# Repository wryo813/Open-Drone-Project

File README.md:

# Open Drone Project
## 概要
このプロジェクトは、Arduinoプラットフォーム上で開発可能なドローン制御システムの構築を目的としています。
***
# ハードウェア
## 電源仕様
### USBバスパワー給電時
- USB Type-C(USB2.0)で供給を行う
- バッテリーの充電が行われる
- バッテリー給電からUSBバスパワー給電に自動的に切り替わる
- システム全体の消費電流が750mAを超えるとリセッタブルヒューズの抵抗値が上がる
- ESP32-WROOM-32とバッテリー残量IC以外のセンサが起動する
- モーターが回転しないようソフト側で制限をかける
### バッテリー給電時
- 供給能力1000mA 3Cの[リチウムイオン二次電池](http://www.kyohritsu.jp/eclib/OTHER/DATASHEET/BATT/dtp603450phr.pdf)から供給を行う
- モーター含むシステム全体に電力を供給する
- すべての負荷はバッテリー残量ICを通過して電力が供給される
- 全モーターの消費電流が3A(仮)を超えたらソフト側で制限をかける
### バッテリー充電
- バッテリー充電はMCP73831-2ATI/OTを用いて行う
- 最大充電電流はPROG-GND間抵抗5kΩで最大200mAに設定する
#### MCP73831-2ATI/OTの最大充電電流の設定([公式データシート](https://www.microchip.jp/docs/DS21984B_JP.pdf)より)
```
IREG=最大充電電流
PROG=最大充電電流設定用抵抗

IREG=1000[V]/PROG[kΩ]
```
原則`最大充電電流[mA]≦バッテリー容量[mAh]`で設定する
### 消費電力
#### USBバスパワー給電時
|負荷 |消費電流 |
|---|---|
|[ESP32-WROOM-32D](https://www.espressif.com/sites/default/files/documentation/esp32-wroom-32_datasheet_en.pdf)|500mA|
|[MCP73831-2ATI/OT](https://www.microchip.jp/docs/DS21984B_JP.pdf)|200mA|
|[BQ27441-G1](http://www.tij.co.jp/jp/lit/ds/symlink/bq27441-g1.pdf)|0mA|
|[FT231XS](https://www.ftdichip.com/Support/Documents/DataSheets/ICs/DS_FT231X.pdf)|8mA|
|[BMX055](https://ae-bst.resource.bosch.com/media/_tech/media/datasheets/BST-BMX055-DS000.pdf)|8mA|
|[AE-VL53L0X](https://www.st.com/content/ccc/resource/technical/document/datasheet/group3/b2/1e/33/77/c6/92/47/6b/DM00279086/files/DM00279086.pdf/jcr:content/translations/en.DM00279086.pdf)|19mA|
|[B0067](http://www.arducam.com/downloads/shields/ArduCAM_Mini_2MP_Camera_Shield_DS.pdf)|70mA|
|[モーター](http://www.vibration-motor.com/products/download/Q7AL2BX180003.pdf)|0mA|
|**合計**|805mA|
#### バッテリー給電時
|負荷 |消費電流 |
|---|---|
|[ESP32-WROOM-32D](https://www.espressif.com/sites/default/files/documentation/esp32-wroom-32_datasheet_en.pdf)|500mA|
|[MCP73831-2ATI/OT](https://www.microchip.jp/docs/DS21984B_JP.pdf)|0mA|
|[BQ27441-G1](http://www.tij.co.jp/jp/lit/ds/symlink/bq27441-g1.pdf)|0.097mA|
|[FT231XS](https://www.ftdichip.com/Support/Documents/DataSheets/ICs/DS_FT231X.pdf)|8mA|
|[BMX055](https://ae-bst.resource.bosch.com/media/_tech/media/datasheets/BST-BMX055-DS000.pdf)|8mA|
|[AE-VL53L0X](https://www.st.com/content/ccc/resource/technical/document/datasheet/group3/b2/1e/33/77/c6/92/47/6b/DM00279086/files/DM00279086.pdf/jcr:content/translations/en.DM00279086.pdf)|19mA|
|[B0067](http://www.arducam.com/downloads/shields/ArduCAM_Mini_2MP_Camera_Shield_DS.pdf)|70mA|
|[モーター](http://www.vibration-motor.com/products/download/Q7AL2BX180003.pdf)|1130.4mA|
|**合計**|1739.097mA|
## 基板仕様
[回路図](https://twitter.com/w_ryo813/status/1123922796239781891)
[基板レイアウト](https://twitter.com/w_ryo813/status/1123887101588774915)
### 基板サイズ
- メイン基板 46×60mm
- 最外サイズ 95×95mm

# ソフトウェア
メインのプログラムは[Drone.ino](https://github.com/wryo813/Open-Drone-Project/blob/master/Drone.ino)
## 通信仕様
- 無線通信はWi-Fiを使って、送信機とドローン本体の一対一で行う
- 送信機とドローン本体は、両方ともAP+STAモードで相互に通信する
- 通信プロトコルはUDPを使用する
- Wi-Fi接続で使用するライブラリは[WiFi.h](https://www.arduino.cc/en/Reference/WiFi)
- UDP通信で使用するライブラリは[WiFiUdp.h](https://github.com/espressif/arduino-esp32/blob/master/libraries/WiFi/src/WiFiUdp.h)
### 送信機から送信するデータ
- 各モーターの目標角度
- YAW軸の目標角速度
- ドローン本体の目標高度
- 緊急停止信号
### ドローン本体から送信するデータ
- バッテリー残量
- 消費電力
- 残り飛行可能時間

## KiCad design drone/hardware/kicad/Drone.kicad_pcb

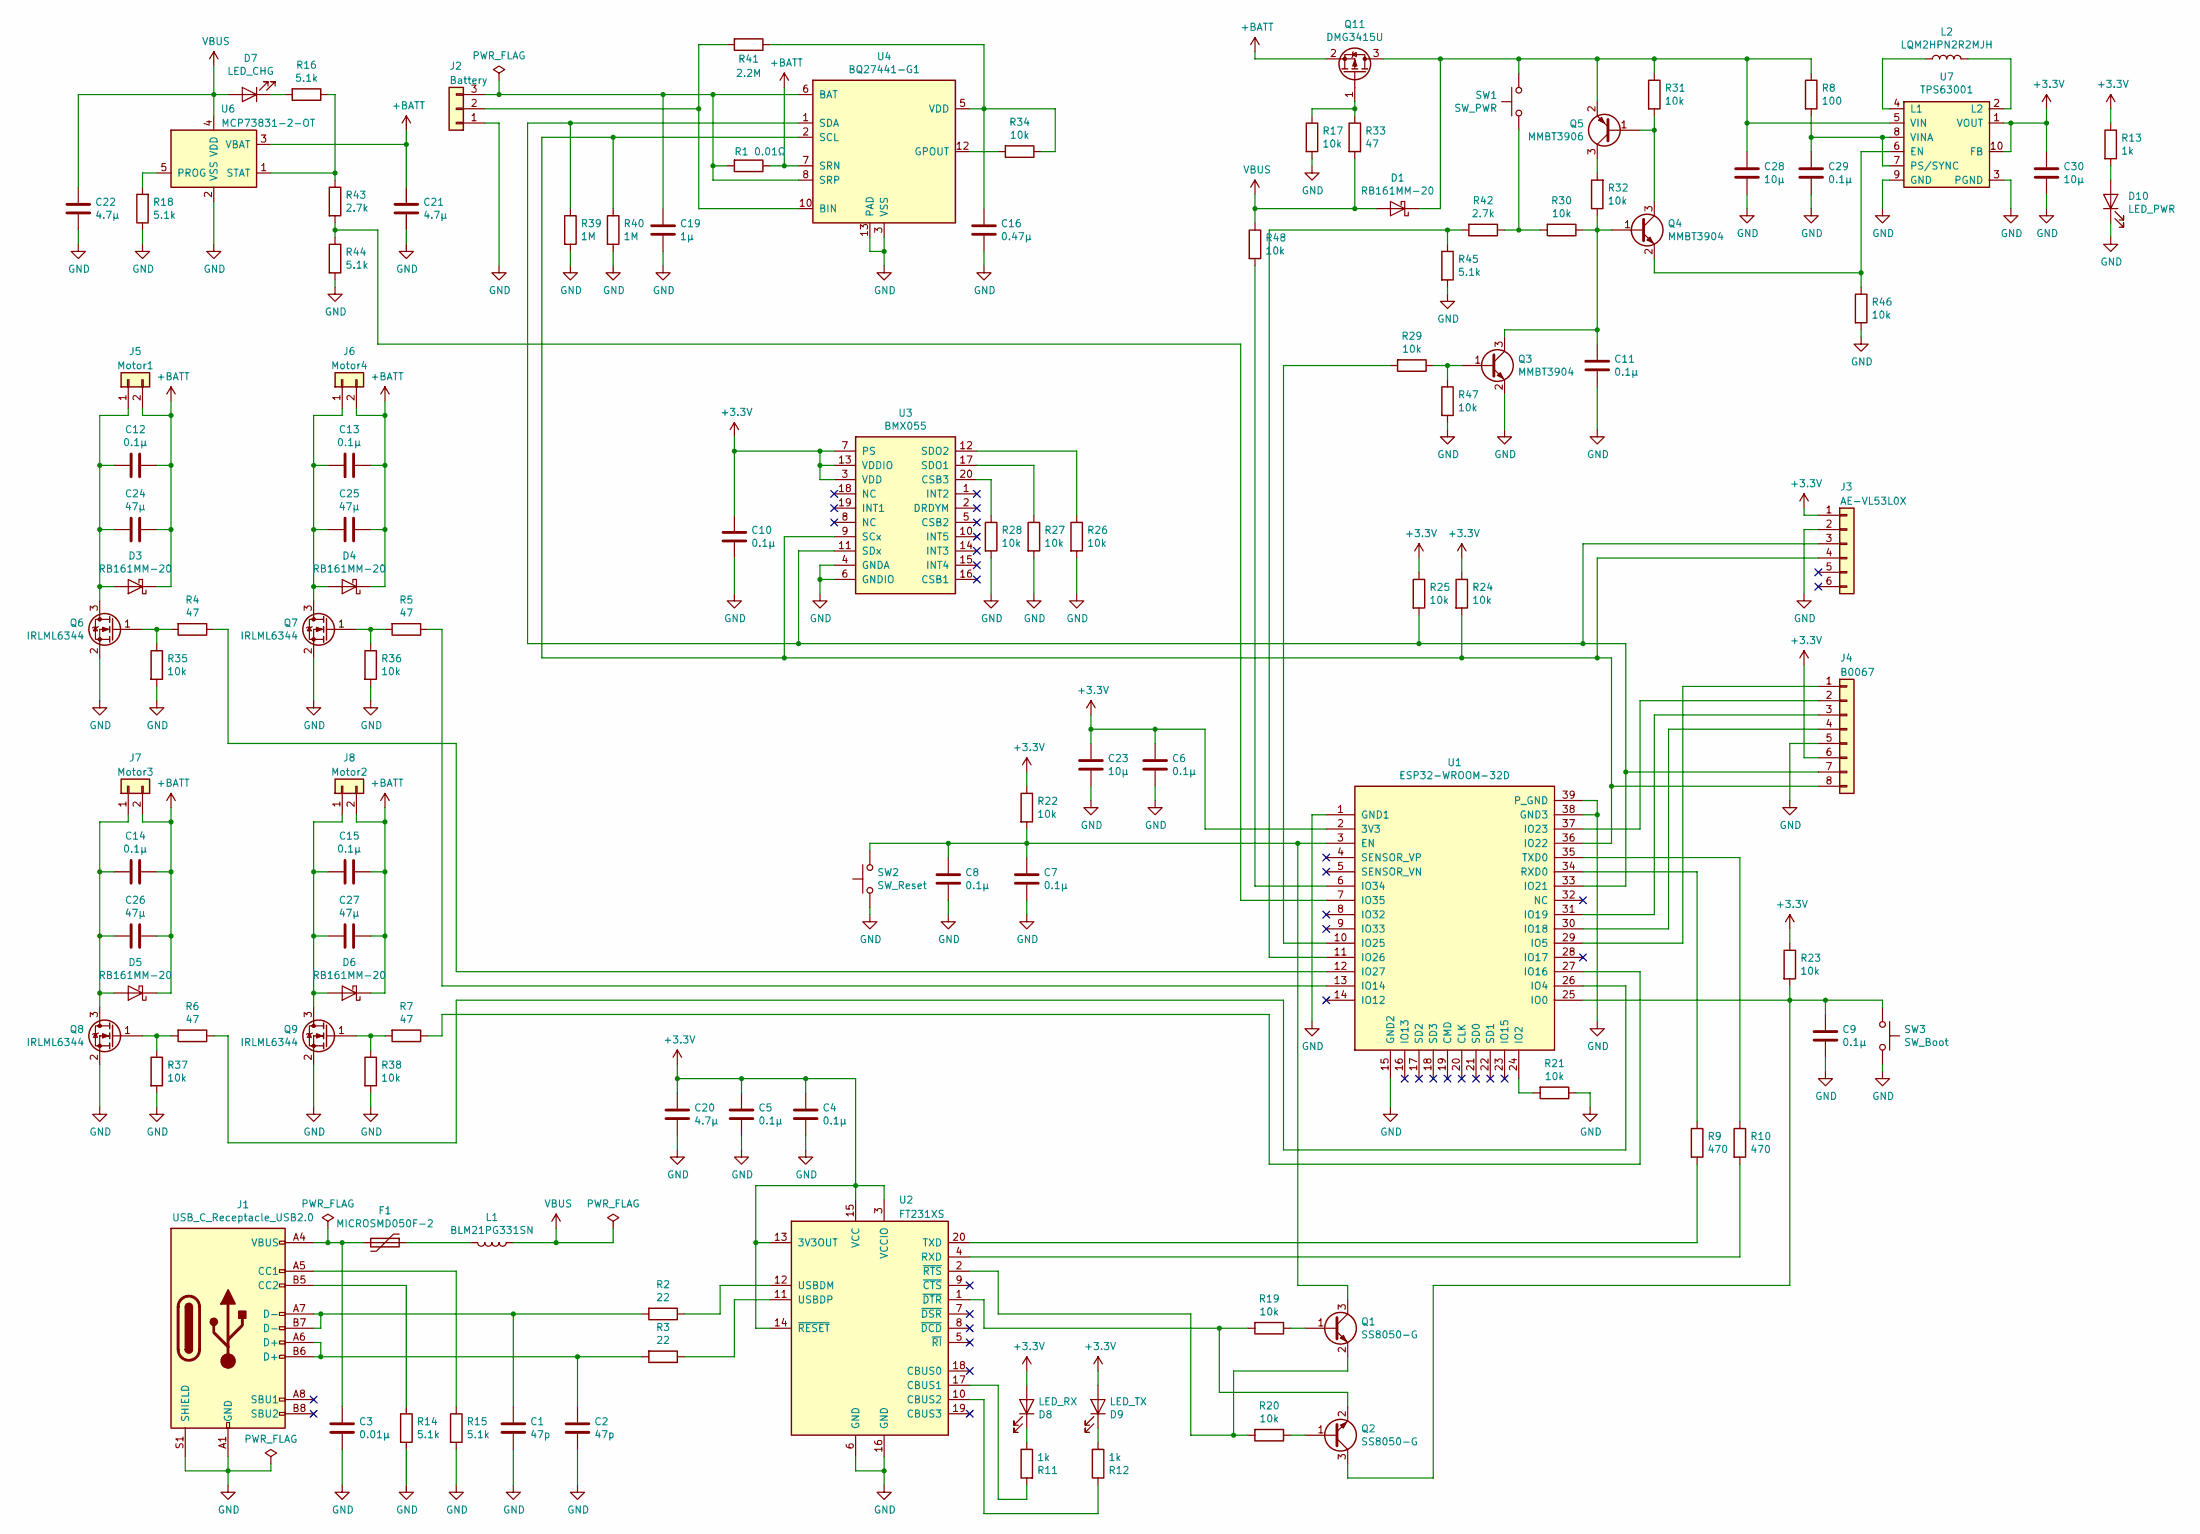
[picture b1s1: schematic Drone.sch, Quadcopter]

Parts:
C1, C2: 47p; C_0603_1608Metric
C3: 0.01μ; C_0603_1608Metric
C4, C5, C6, C7, C8, C9, C10, C11, C12, C13, C14, C15, C29: 0.1μ; C_0603_1608Metric
C16: 0.47μ; C_0603_1608Metric
C19: 1μ; C_0603_1608Metric
C20, C21, C22: 4.7μ; C_0603_1608Metric
C23, C28, C30: 10μ; C_0603_1608Metric
C24, C25, C26, C27: 47μ; C_1210_3225Metric
D1, D3, D4, D5, D6: RB161MM-20; D_SOD-123F
D7: LED_CHG; LED_0603_1608Metric_Castellated
D8: LED_RX; LED_0603_1608Metric_Castellated
D9: LED_TX; LED_0603_1608Metric_Castellated
D10: LED_PWR; LED_0603_1608Metric_Castellated
F1: MICROSMD050F-2; Fuse_1210_3225Metric
J1: USB_C_Receptacle_USB2.0; USB_C_Receptacle_Amphenol_12401610E4-2A
J2: Battery; JST_PH_S3B-PH-SM4-TB_1x03-1MP_P2.00mm_Horizontal
J3: AE-VL53L0X; JST_S6B-ZR-SM4A-TF(LF)(SN)
J4: B0067; JST_PH_S8B-PH-SM4-TB_1x08-1MP_P2.00mm_Horizontal
J5: Motor1; JST_SHL_SM02B-SHLS-TF_1x02-1MP_P1.00mm_Horizontal
J6: Motor4; JST_SHL_SM02B-SHLS-TF_1x02-1MP_P1.00mm_Horizontal
J7: Motor3; JST_SHL_SM02B-SHLS-TF_1x02-1MP_P1.00mm_Horizontal
J8: Motor2; JST_SHL_SM02B-SHLS-TF_1x02-1MP_P1.00mm_Horizontal
L1: BLM21PG331SN; L_0805_2012Metric
L2: LQM2HPN2R2MJH; INDC2520X100
Q1, Q2: SS8050-G; SOT-23
Q3, Q4: MMBT3904; SOT-23
Q5: MMBT3906; SOT-23
Q6, Q7, Q8, Q9: IRLML6344; SOT-23
Q11: DMG3415U; SOT-23
R1: 0.01Ω; R_1206_3216Metric
R2, R3: 22; R_0603_1608Metric
R4, R5, R6, R7, R33: 47; R_0603_1608Metric
R8: 100; R_0603_1608Metric
R9, R10: 470; R_0603_1608Metric
R11, R12, R13: 1k; R_0603_1608Metric
R14, R15, R16, R18, R44, R45: 5.1k; R_0603_1608Metric
R17, R19, R20, R21, R22, R23, R24, R25, R26, R27, R28, R29, R30, R31, R32, R34, R35, R36, R37, R38, R46, R47, R48: 10k; R_0603_1608Metric
R39, R40: 1M; R_0603_1608Metric
R41: 2.2M; R_0603_1608Metric
R42, R43: 2.7k; R_0603_1608Metric
SW1: SW_PWR; SW_SKRPACE010
SW2: SW_Reset; SW_SKRPACE010
SW3: SW_Boot; SW_SKRPACE010
U1: ESP32-WROOM-32D; ESP32-WROOM-32
U2: FT231XS; SSOP-20_3.9x8.7mm_P0.635mm
U3: BMX055; PQFN50P450X300X100-20N
U4: BQ27441-G1; Texas_S-PDSO-N12
U6: MCP73831-2-OT; SOT-23-5
U7: TPS63001; Texas_S-PVSON-N10

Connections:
+3V3: C4.1, C5.1, C6.1, C10.1, C20.1, C23.1, C30.1, D8.2 (A), D9.2 (A), J3.1, J4.6, R13.1, R22.1, R23.1, R24.1, R25.1, U1.2 (3V3), U2.3 (VCCIO), U2.13 (3V3OUT), U2.14 (~RESET), U2.15 (VCC), U3.3 (VDD), U3.7 (PS), U3.13 (VDDIO), U7.1 (VOUT), U7.10 (FB)
+BATT: C12.1, C13.1, C14.1, C15.1, C21.1, C24.1, C25.1, C26.1, C27.1, D3.1 (K), D4.1 (K), D5.1 (K), D6.1 (K), J5.2, J6.2, J7.2, J8.2, Q11.2 (S), R1.1, U4.7 (SRN), U6.3 (VBAT)
GND: C1.2, C2.2, C3.2, C4.2, C5.2, C6.2, C7.2, C8.2, C9.2, C10.2, C11.2, C16.2, C19.2, C20.2, C21.2, C22.2, C23.2, C28.2, C29.2, C30.2, D10.1 (K), J1.A1 (GND), J1.A12 (GND), J1.B1 (GND), J1.B12 (GND), J1.S1 (SHIELD), J2.1, J3.2, J4.5, Q3.2 (E), Q6.2 (S), Q7.2 (S), Q8.2 (S), Q9.2 (S), R14.2, R15.2, R17.2, R18.1, R21.1, R26.2, R27.2, R28.2, R35.2, R36.2, R37.2, R38.2, R39.2, R40.2, R44.2, R45.2, R46.2, R47.2, SW2.1, SW3.2, U1.1 (GND1), U1.15 (GND2), U1.38 (GND3), U1.39 (P_GND), U2.6 (GND), U2.16 (GND), U3.4 (GNDA), U3.6 (GNDIO), U4.3 (VSS), U4.13 (PAD), U6.2 (VSS), U7.3 (PGND), U7.9 (GND), U7.11
unnamed: C1.1, J1.A7 (D-), J1.B7 (D-), R2.2
unnamed: C2.1, J1.A6 (D+), J1.B6 (D+), R3.2
unnamed: C3.1, F1.2, J1.A4 (VBUS), J1.A9 (VBUS), J1.B4 (VBUS), J1.B9 (VBUS)
unnamed: C7.1, C8.1, Q1.3 (C), R22.2, SW2.2, U1.3 (EN)
unnamed: C9.1, Q2.3 (C), R23.2, SW3.1, U1.25 (IO0)
unnamed: C11.1, Q3.3 (C), Q4.1 (B), R30.1, R32.1
unnamed: C12.2, C24.2, D3.2 (A), J5.1, Q6.3 (D)
unnamed: C13.2, C25.2, D4.2 (A), J6.1, Q7.3 (D)
unnamed: C14.2, C26.2, D5.2 (A), J7.1, Q8.3 (D)
unnamed: C15.2, C27.2, D6.2 (A), J8.1, Q9.3 (D)
unnamed: C16.1, R34.1, R41.1, U4.5 (VDD)
unnamed: C19.1, J2.3, R1.2, U4.6 (BAT), U4.8 (SRP)
unnamed: C28.1, D1.1 (K), Q5.2 (E), Q11.3 (D), R8.1, R31.1, SW1.1, U7.5 (VIN)
unnamed: C29.1, R8.2, U7.7 (PS/SYNC), U7.8 (VINA)
unnamed: D7.1 (K), R16.2
unnamed: D8.1 (K), R11.1
unnamed: D9.1 (K), R12.2
unnamed: D10.2 (A), R13.2
unnamed: F1.1, L1.2
unnamed: J1.A5 (CC1), R15.1
unnamed: J1.B5 (CC2), R14.1
unnamed: J2.2, R41.2, U4.10 (BIN)
unnamed: J3.3, J4.7, R25.2, R39.1, U1.33 (IO21), U3.11 (SDx), U4.1 (SDA)
unnamed: J3.4, J4.8, R24.2, R40.1, U1.36 (IO22), U3.9 (SCx), U4.2 (SCL)
unnamed: J4.1, U1.29 (IO5)
unnamed: J4.2, U1.37 (IO23)
unnamed: J4.3, U1.31 (IO19)
unnamed: J4.4, U1.30 (IO18)
unnamed: L2.1, U7.4 (L1)
unnamed: L2.2, U7.2 (L2)
unnamed: Q1.1 (B), R19.1
unnamed: Q1.2 (E), R20.2, U2.2 (~RTS)
unnamed: Q2.1 (B), R20.1
unnamed: Q2.2 (E), R19.2, U2.1 (~DTR)
unnamed: Q3.1 (B), R29.1, R47.1
unnamed: Q4.2 (E), R46.1, U7.6 (EN)
unnamed: Q4.3 (C), Q5.1 (B), R31.2
unnamed: Q5.3 (C), R32.2
unnamed: Q6.1 (G), R4.2, R35.1
unnamed: Q7.1 (G), R5.2, R36.1
unnamed: Q8.1 (G), R6.2, R37.1
unnamed: Q9.1 (G), R7.2, R38.1
unnamed: Q11.1 (G), R17.1, R33.1
unnamed: R2.1, U2.12 (USBDM)
unnamed: R3.1, U2.11 (USBDP)
unnamed: R4.1, U1.12 (IO27)
unnamed: R5.1, U1.13 (IO14)
unnamed: R6.1, U1.26 (IO4)
unnamed: R7.1, U1.27 (IO16)
unnamed: R9.1, U1.34 (RXD0)
unnamed: R9.2, U2.20 (TXD)
unnamed: R10.1, U1.35 (TXD0)
unnamed: R10.2, U2.4 (RXD)
unnamed: R11.2, U2.17 (CBUS1)
unnamed: R12.1, U2.10 (CBUS2)
unnamed: R16.1, R43.1, U6.1 (STAT)
unnamed: R18.2, U6.5 (PROG)
unnamed: R21.2, U1.24 (IO2)
unnamed: R26.1, U3.12 (SDO2)
unnamed: R27.1, U3.17 (SDO1)
unnamed: R28.1, U3.20 (CSB3)
unnamed: R29.2, U1.10 (IO25)
unnamed: R30.2, R42.1, SW1.2
unnamed: R34.2, U4.12 (GPOUT)
unnamed: R42.2, R45.1, U1.11 (IO26)
unnamed: R43.2, R44.1, U1.7 (IO35)
unnamed: R48.2, U1.6 (IO34)
VBUS: C22.1, D1.2 (A), D7.2 (A), L1.1, R33.2, R48.1, U6.4 (VDD)

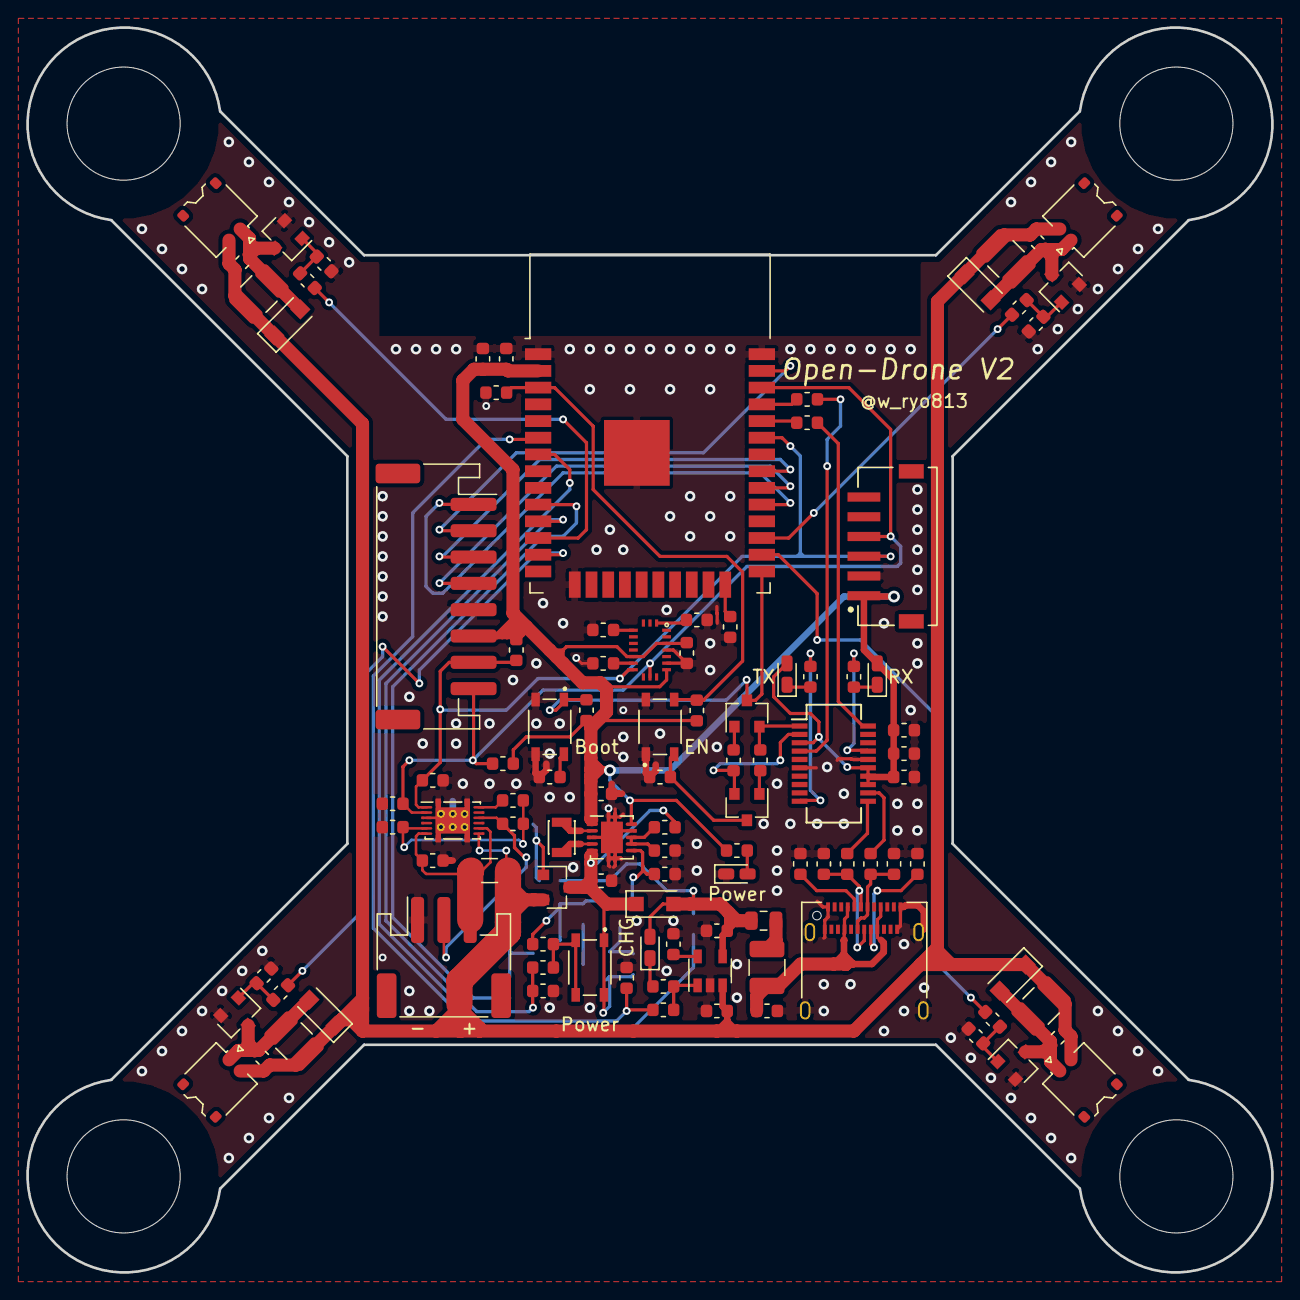
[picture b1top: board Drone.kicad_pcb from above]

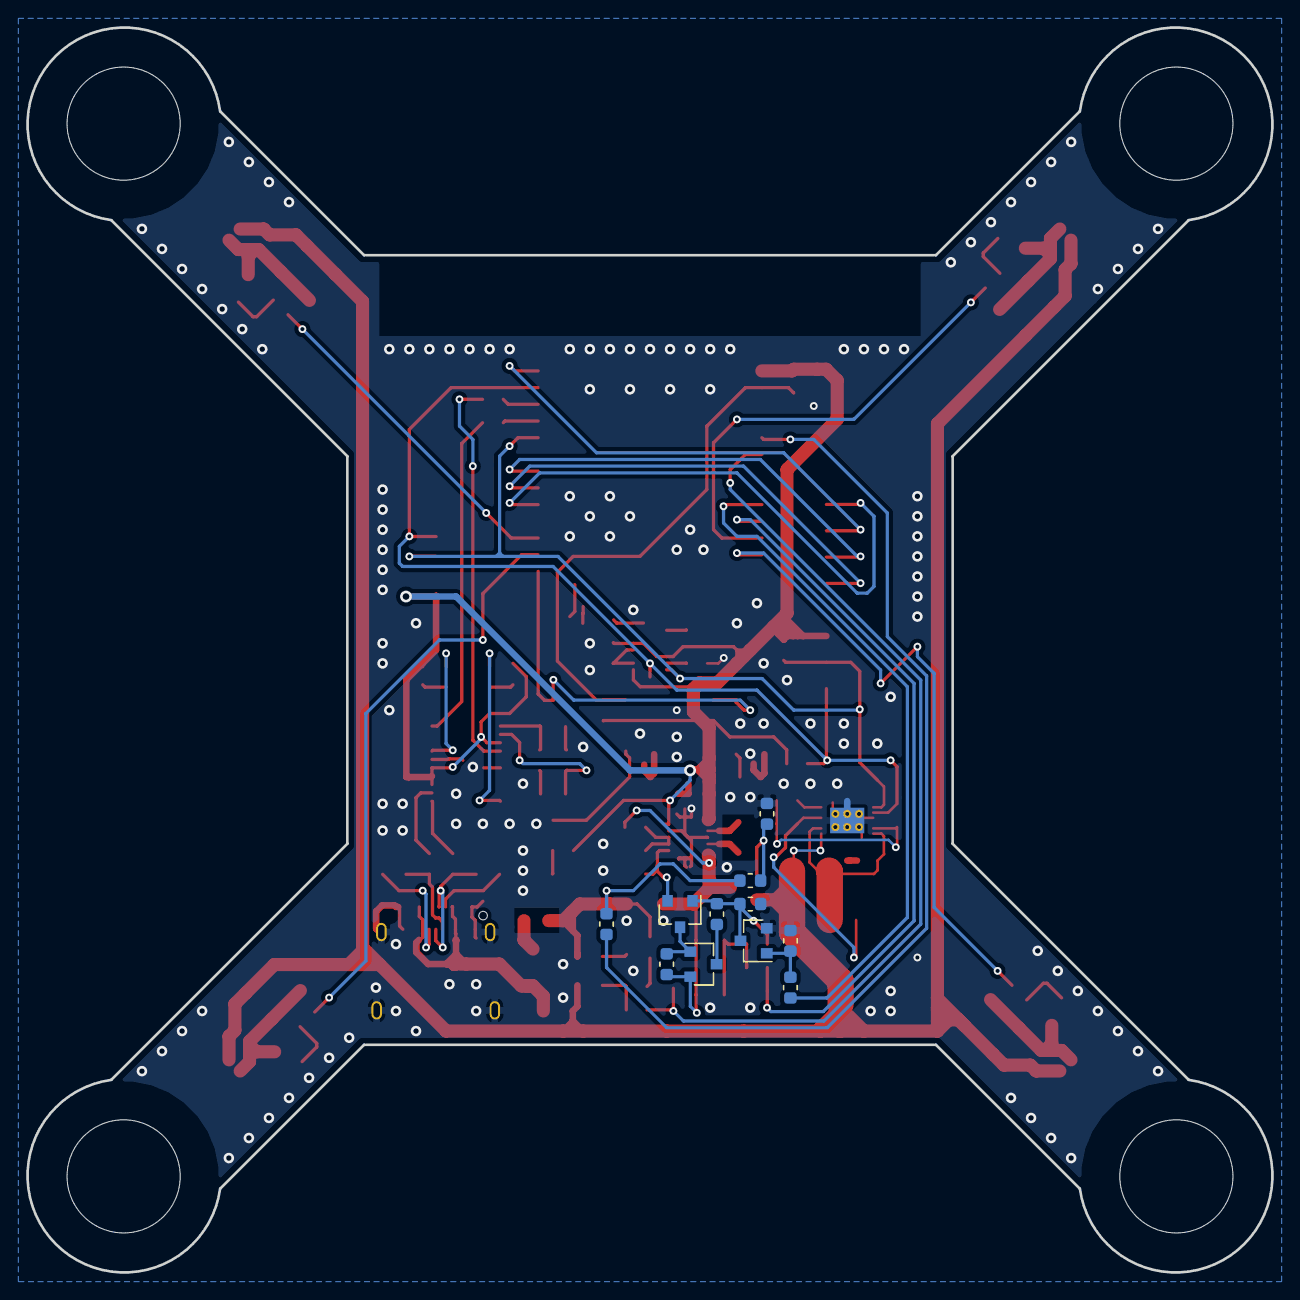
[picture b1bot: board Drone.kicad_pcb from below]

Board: 2 copper layers, 94.6 x 94.6 mm, 115 parts (11 on the bottom side), 71 nets.

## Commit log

2019-03-17 test
2019-03-17 test2
2019-03-17 hoge
2019-03-17 デフォルト
2019-03-17 vscodeから
2019-05-06 ジャイロのレンジ変更
2019-05-06 シリアル通信を500000bpsに変更
2019-05-06 Bandwidth 変更
2019-05-10 md変更
2019-05-21 i2cAddr
2019-05-29 ファイル構成変更
2019-06-02 文字列分割
2019-06-02 文字列分割の高速化
2019-06-07 元バージョン
2019-06-23 電源スイッチ外部割込み動かん
2019-06-23 電源スイッチ外部割り込みやめた
2019-07-04 memo2
2019-07-06 IMUは動く
2019-07-09 モーターごとに角度を送信
2019-07-13 PD制御を実装
2019-07-20 PID制御の実装
2019-07-28 コメント
2019-07-31 yaw軸PID実装
